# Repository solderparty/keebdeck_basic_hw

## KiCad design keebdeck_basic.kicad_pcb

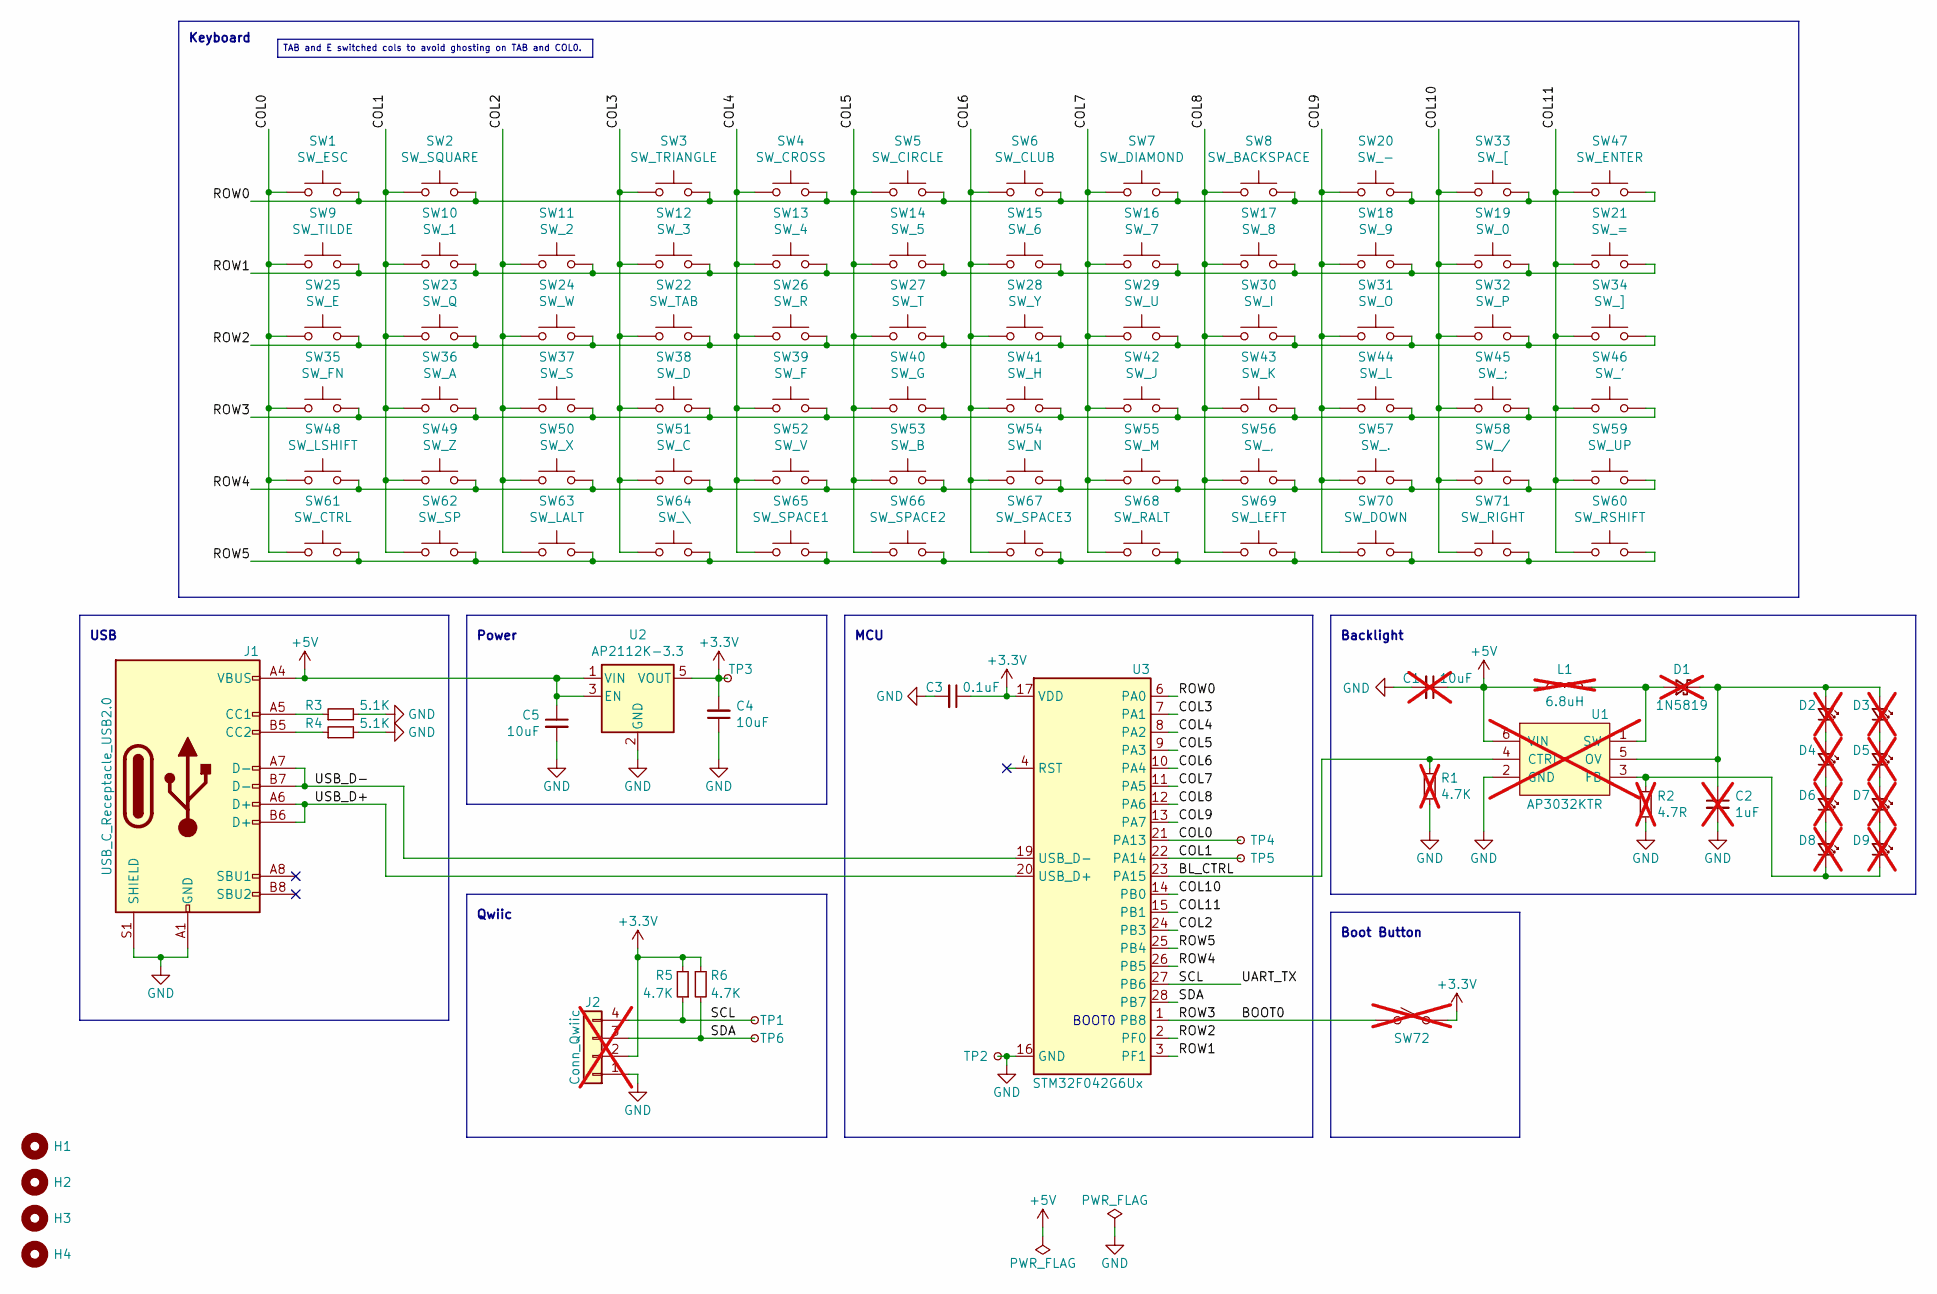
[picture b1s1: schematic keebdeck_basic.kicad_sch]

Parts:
C1: 10uF; C_0603_1608Metric; not fitted
C2: 1uF; C_0603_1608Metric; not fitted
C3: 0.1uF; C_0603_1608Metric
C4, C5: 10uF; C_0603_1608Metric
D1: 1N5819; D_SOD-323_HandSoldering; LCSC C369937; not fitted
D2, D3, D4, D5, D6, D7, D8, D9: LTW-010DCG-SR-G; LCSC C5175311; not fitted
H1, H2, H3, H4: MountingHole; SMD-1_BD4.4-D2.8; LCSC C5301775
J1: USB_C_Receptacle_USB2.0; USB_C_Receptacle_SHOU_HAN-TYPE-C-16P-CB1.6-073; LCSC C2906290
J2: Conn_Qwiic; JST_SH_SM04B-SRSS-TB_1x04-1MP_P1.00mm_Horizontal; LCSC C145956; not fitted
L1: 6.8uH; L_1008_2520Metric; LCSC C2041474; not fitted
R1: 4.7K; R_0603_1608Metric; not fitted
R2: 4.7R; R_0603_1608Metric; not fitted
R3, R4: 5.1K; R_0603_1608Metric
R5, R6: 4.7K; R_0603_1608Metric
SW1: SW_ESC; Metal_Dome_Oblong_5x4mm
SW2: SW_SQUARE; Metal_Dome_Oblong_5x4mm
SW3: SW_TRIANGLE; Metal_Dome_Oblong_5x4mm
SW4: SW_CROSS; Metal_Dome_Oblong_5x4mm
SW5: SW_CIRCLE; Metal_Dome_Oblong_5x4mm
SW6: SW_CLUB; Metal_Dome_Oblong_5x4mm
SW7: SW_DIAMOND; Metal_Dome_Oblong_5x4mm
SW8: SW_BACKSPACE; Metal_Dome_Oblong_5x4mm
SW9: SW_TILDE; Metal_Dome_Oblong_5x4mm
SW10: SW_1; Metal_Dome_Oblong_5x4mm
SW11: SW_2; Metal_Dome_Oblong_5x4mm
SW12: SW_3; Metal_Dome_Oblong_5x4mm
SW13: SW_4; Metal_Dome_Oblong_5x4mm
SW14: SW_5; Metal_Dome_Oblong_5x4mm
SW15: SW_6; Metal_Dome_Oblong_5x4mm
SW16: SW_7; Metal_Dome_Oblong_5x4mm
SW17: SW_8; Metal_Dome_Oblong_5x4mm
SW18: SW_9; Metal_Dome_Oblong_5x4mm
SW19: SW_0; Metal_Dome_Oblong_5x4mm
SW20: SW_-; Metal_Dome_Oblong_5x4mm
SW21: SW_=; Metal_Dome_Oblong_5x4mm
SW22: SW_TAB; Metal_Dome_Oblong_5x4mm
SW23: SW_Q; Metal_Dome_Oblong_5x4mm
SW24: SW_W; Metal_Dome_Oblong_5x4mm
SW25: SW_E; Metal_Dome_Oblong_5x4mm
SW26: SW_R; Metal_Dome_Oblong_5x4mm
SW27: SW_T; Metal_Dome_Oblong_5x4mm
SW28: SW_Y; Metal_Dome_Oblong_5x4mm
SW29: SW_U; Metal_Dome_Oblong_5x4mm
SW30: SW_I; Metal_Dome_Oblong_5x4mm
SW31: SW_O; Metal_Dome_Oblong_5x4mm
SW32: SW_P; Metal_Dome_Oblong_5x4mm
SW33: SW_[; Metal_Dome_Oblong_5x4mm
SW34: SW_]; Metal_Dome_Oblong_5x4mm
SW35: SW_FN; Metal_Dome_Oblong_5x4mm
SW36: SW_A; Metal_Dome_Oblong_5x4mm
SW37: SW_S; Metal_Dome_Oblong_5x4mm
SW38: SW_D; Metal_Dome_Oblong_5x4mm
SW39: SW_F; Metal_Dome_Oblong_5x4mm
SW40: SW_G; Metal_Dome_Oblong_5x4mm
SW41: SW_H; Metal_Dome_Oblong_5x4mm
SW42: SW_J; Metal_Dome_Oblong_5x4mm
SW43: SW_K; Metal_Dome_Oblong_5x4mm
SW44: SW_L; Metal_Dome_Oblong_5x4mm
SW45: SW_;; Metal_Dome_Oblong_5x4mm
SW46: SW_'; Metal_Dome_Oblong_5x4mm
SW47: SW_ENTER; Metal_Dome_Oblong_5x4mm
SW48: SW_LSHIFT; Metal_Dome_Oblong_5x4mm
SW49: SW_Z; Metal_Dome_Oblong_5x4mm
SW50: SW_X; Metal_Dome_Oblong_5x4mm
SW51: SW_C; Metal_Dome_Oblong_5x4mm
SW52: SW_V; Metal_Dome_Oblong_5x4mm
SW53: SW_B; Metal_Dome_Oblong_5x4mm
SW54: SW_N; Metal_Dome_Oblong_5x4mm
SW55: SW_M; Metal_Dome_Oblong_5x4mm
SW56: SW_,; Metal_Dome_Oblong_5x4mm
SW57: SW_.; Metal_Dome_Oblong_5x4mm
SW58: SW_/; Metal_Dome_Oblong_5x4mm
SW59: SW_UP; Metal_Dome_Oblong_5x4mm
SW60: SW_RSHIFT; Metal_Dome_Oblong_5x4mm
SW61: SW_CTRL; Metal_Dome_Oblong_5x4mm
SW62: SW_SP; Metal_Dome_Oblong_5x4mm
SW63: SW_LALT; Metal_Dome_Oblong_5x4mm
SW64: SW_\; Metal_Dome_Oblong_5x4mm
SW65: SW_SPACE1; Metal_Dome_Oblong_5x4mm
SW66: SW_SPACE2; Metal_Dome_Oblong_5x4mm
SW67: SW_SPACE3; Metal_Dome_Oblong_5x4mm
SW68: SW_RALT; Metal_Dome_Oblong_5x4mm
SW69: SW_LEFT; Metal_Dome_Oblong_5x4mm
SW70: SW_DOWN; Metal_Dome_Oblong_5x4mm
SW71: SW_RIGHT; Metal_Dome_Oblong_5x4mm
SW72: SW_BOOT; TS-1088R; LCSC C455280; not fitted
TP1: TP_SCL; TestPoint_Pad_D1.5mm
TP2, TP3: TP_UART_TX; TestPoint_Pad_D1.5mm
TP4: TP_SWDIO; TestPoint_Pad_D1.5mm
TP5: TP_SWCLK; TestPoint_Pad_D1.5mm
TP6: TP_SDA; TestPoint_Pad_D1.5mm
U1: AP3032KTR; SOT-23-6; LCSC C264086; not fitted
U2: AP2112K-3.3; SOT-23-5; LCSC C51118
U3: STM32F042G6Ux; QFN-28_4x4mm_P0.5mm; LCSC C961597

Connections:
+3.3V: C3.1, C4.2, J2.2, R5.2, R6.1, SW72.1 (A), TP3.1, U2.5 (VOUT), U3.5 (VDDA), U3.17 (VDD), U3.18 (VDDIO2)
+5V: C1.1, C5.1, J1.A4 (VBUS), J1.A9 (VBUS), J1.B4 (VBUS), J1.B9 (VBUS), L1.1, U1.6 (VIN), U2.1 (VIN), U2.3 (EN)
/BL_CTRL: R1.2, U1.4 (CTRL), U3.23 (PA15)
/BOOT0: SW35.2, SW36.2, SW37.2, SW38.2, SW39.2, SW40.2, SW41.2, SW42.2, SW43.2, SW44.2, SW45.2, SW46.2, SW72.2 (B), U3.1 (PB8)
/COL0: SW1.1, SW9.1, SW25.1, SW35.1, SW48.1, SW61.1, TP4.1, U3.21 (PA13)
/COL1: SW2.1, SW10.1, SW23.1, SW36.1, SW49.1, SW62.1, TP5.1, U3.22 (PA14)
/COL2: SW11.1, SW24.1, SW37.1, SW50.1, SW63.1, U3.24 (PB3)
/COL3: SW3.1, SW12.1, SW22.1, SW38.1, SW51.1, SW64.1, U3.7 (PA1)
/COL4: SW4.1, SW13.1, SW26.1, SW39.1, SW52.1, SW65.1, U3.8 (PA2)
/COL5: SW5.1, SW14.1, SW27.1, SW40.1, SW53.1, SW66.1, U3.9 (PA3)
/COL6: SW6.1, SW15.1, SW28.1, SW41.1, SW54.1, SW67.1, U3.10 (PA4)
/COL7: SW7.1, SW16.1, SW29.1, SW42.1, SW55.1, SW68.1, U3.11 (PA5)
/COL8: SW8.1, SW17.1, SW30.1, SW43.1, SW56.1, SW69.1, U3.12 (PA6)
/COL9: SW18.1, SW20.1, SW31.1, SW44.1, SW57.1, SW70.1, U3.13 (PA7)
/COL10: SW19.1, SW32.1, SW33.1, SW45.1, SW58.1, SW71.1, U3.14 (PB0)
/COL11: SW21.1, SW34.1, SW46.1, SW47.1, SW59.1, SW60.1, U3.15 (PB1)
/ROW0: SW1.2, SW2.2, SW3.2, SW4.2, SW5.2, SW6.2, SW7.2, SW8.2, SW20.2, SW33.2, SW47.2, U3.6 (PA0)
/ROW1: SW9.2, SW10.2, SW11.2, SW12.2, SW13.2, SW14.2, SW15.2, SW16.2, SW17.2, SW18.2, SW19.2, SW21.2, U3.3 (PF1)
/ROW2: SW22.2, SW23.2, SW24.2, SW25.2, SW26.2, SW27.2, SW28.2, SW29.2, SW30.2, SW31.2, SW32.2, SW34.2, U3.2 (PF0)
/ROW4: SW48.2, SW49.2, SW50.2, SW51.2, SW52.2, SW53.2, SW54.2, SW55.2, SW56.2, SW57.2, SW58.2, SW59.2, U3.26 (PB5)
/ROW5: SW60.2, SW61.2, SW62.2, SW63.2, SW64.2, SW65.2, SW66.2, SW67.2, SW68.2, SW69.2, SW70.2, SW71.2, U3.25 (PB4)
/SCL: J2.4, R5.1, TP1.1, U3.27 (PB6)
/SDA: J2.3, R6.2, TP6.1, U3.28 (PB7)
/USB_D+: J1.A6 (D+), J1.B6 (D+), U3.20 (USB_D+)
/USB_D-: J1.A7 (D-), J1.B7 (D-), U3.19 (USB_D-)
GND: C1.2, C2.2, C3.2, C4.1, C5.2, J1.A1 (GND), J1.A12 (GND), J1.B1 (GND), J1.B12 (GND), J1.S1 (SHIELD), J2.1, R1.1, R2.2, R3.2, R4.2, TP2.1, U1.2 (GND), U2.2 (GND), U3.16 (GND)
unnamed: D1.2 (A), L1.2, U1.1 (SW)
unnamed: C2.1, D1.1 (K), D2.2 (A), D3.2 (A), U1.5 (OV)
unnamed: D2.1 (K), D4.2 (A)
unnamed: D3.1 (K), D5.2 (A)
unnamed: D4.1 (K), D6.2 (A)
unnamed: D5.1 (K), D7.2 (A)
unnamed: D6.1 (K), D8.2 (A)
unnamed: D7.1 (K), D9.2 (A)
unnamed: D8.1 (K), D9.1 (K), R2.1, U1.3 (FB)
unnamed: J1.A5 (CC1), R3.1
unnamed: J1.B5 (CC2), R4.1

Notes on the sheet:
Keyboard
Boot Button
USB
Backlight
Qwiic
BOOT0
MCU
Power
TAB and E switched cols to avoid ghosting on TAB and COL0.

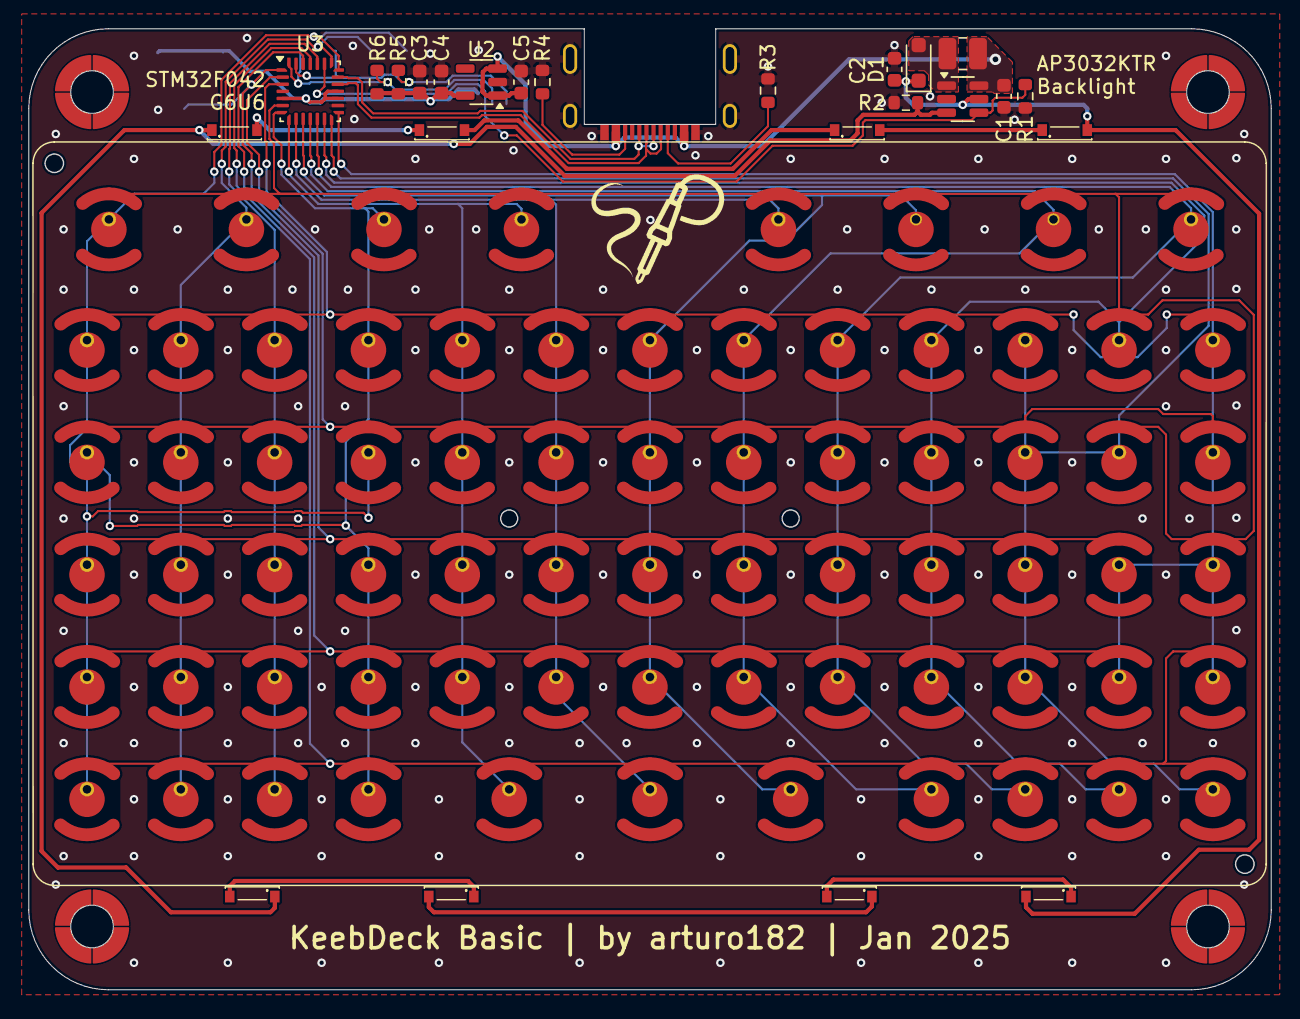
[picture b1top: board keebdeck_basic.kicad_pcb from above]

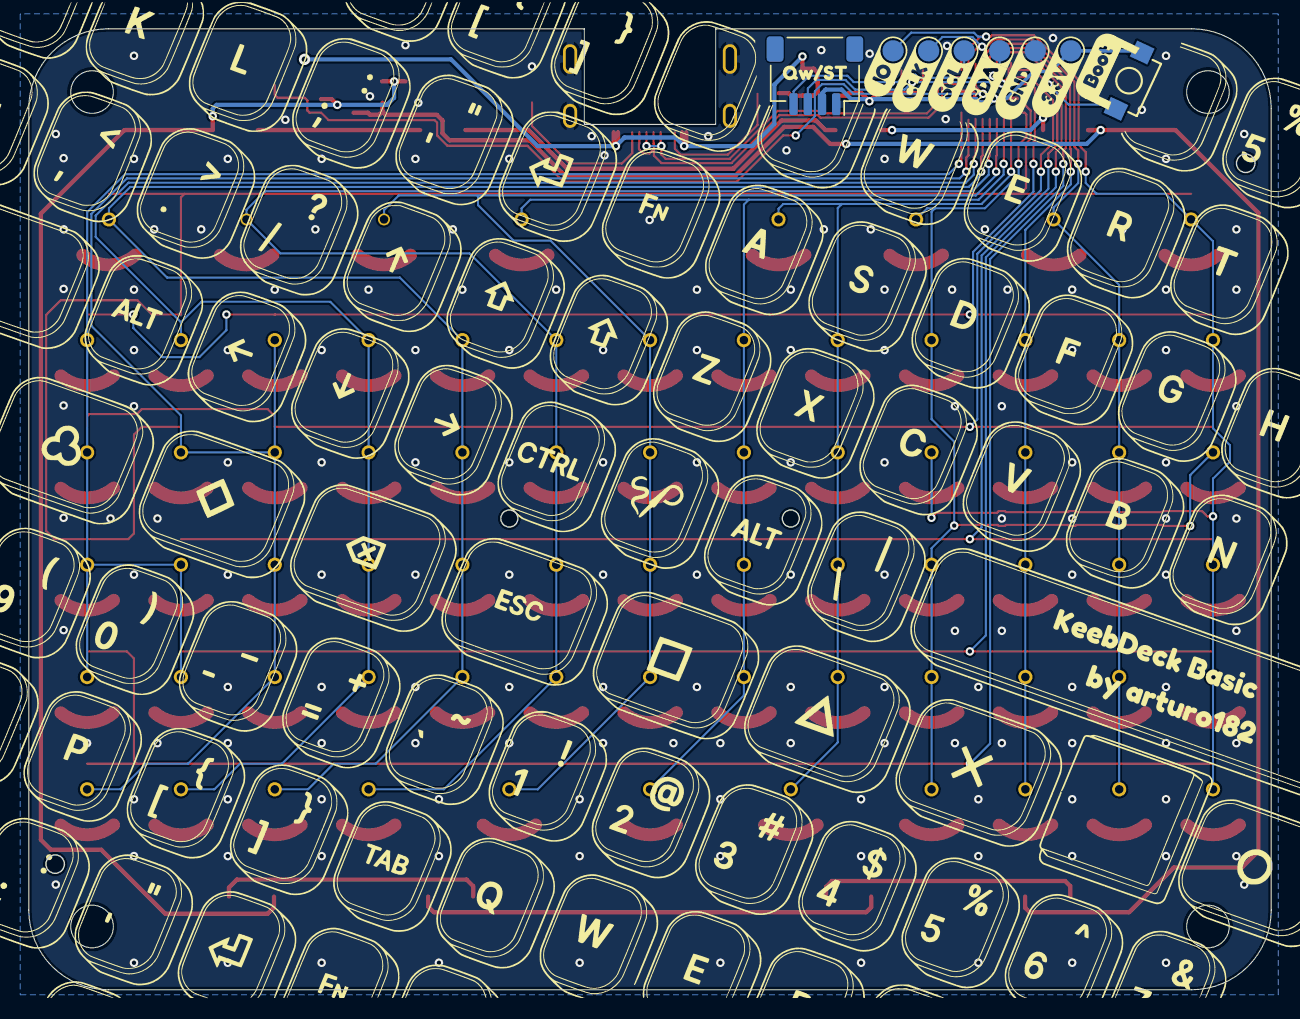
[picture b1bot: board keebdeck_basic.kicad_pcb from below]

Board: 2 copper layers, 87.4 x 67.6 mm, 118 parts (18 on the bottom side), 37 nets.

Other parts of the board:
kibuzzard-66E774B8: G***; kibuzzard-66E774B8
kibuzzard-67980A86: G***; kibuzzard-67980A86
kibuzzard-67980AB3: G***; kibuzzard-67980AB3
kibuzzard-67980AD7: G***; kibuzzard-67980AD7
kibuzzard-67980AE1: G***; kibuzzard-67980AE1
kibuzzard-67980AE6: G***; kibuzzard-67980AE6
kibuzzard-67980B11: G***; kibuzzard-67980B11
kibuzzard-67991D89: G***; kibuzzard-67991D89
kibuzzard-67991E3A: G***; kibuzzard-67991E3A
kibuzzard-6798348F: G***; kibuzzard-6798348F

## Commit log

2025-11-11 Efficiency and EMI improvements
    Changed the voltage supply for the backlight from +3.3V to +5V. This should improve the power efficiency slightly, as the AP3032 is more efficient at 5V input, and the LDO needs to handle less curren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
    Also added vias next to the GND pads of the USB-C connector, this might slightly improve EMI at no extra costs.
